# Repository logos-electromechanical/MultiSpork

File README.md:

MultiSpork
==========

A wireless analog/digital multitool &amp; data recorder.

When I'm working on a mobile robotics projects, I often wish I could attach my scope, logic analyzer, or signal generator to some aspect of the 'bot without tethering it to the bench. IOW, what I need is some kind of widget that does the data acquisition on the 'bot and sends it back to a screen. Ideally, it would also have plenty of range, easy configuration, a nice interface (Saleae is my model for how this should be). 

Maxim just released a chip, the MAX 11300, that incorporates a good chunk of what's required for this. It gives you twenty channels, each of which can by ADC, DAC, or GPIO, and communicates over a fast SPI bus. Add an Atmel SAM processor (I already have the dev tools, so this is an easy decision) and a wifi module, and we're in business. Cheap wifi-only Android tablets can be had for as little as $50, so Android is the obvious choice for a host OS. 

See the MultiSpork/documentation/MultiSporkSystemDescription.md for more info. This will go into the wiki when it's complete.

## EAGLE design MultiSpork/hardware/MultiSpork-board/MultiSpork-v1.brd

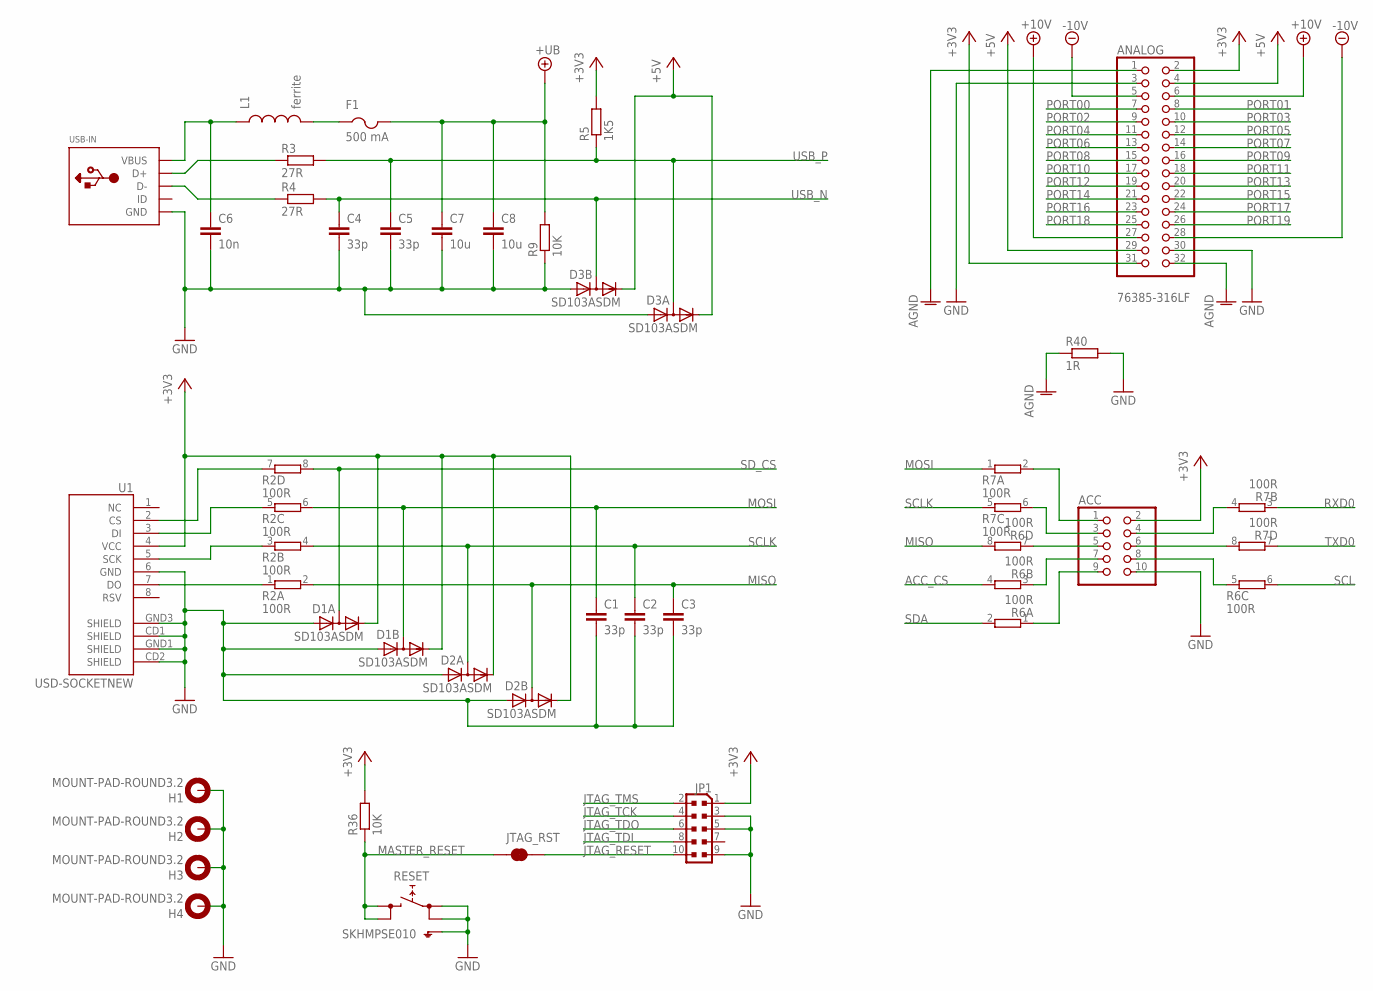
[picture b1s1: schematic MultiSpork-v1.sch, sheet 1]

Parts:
ACC: PINHD-2X5_2.54; 2X05; PARTNO *
ANALOG: 76385-316LF; 32P-SIDE-SMD; PARTNO 76385-316LF
C1, C2, C3, C4, C5: 33p; C0603; PARTNO VJ0603A330JXACW1BC
C6: 10n; C0603; PARTNO CL10B103KB8NCNC
C7, C8: 10u; C1206; PARTNO C3216X5R1E106M
D1, D2, D3: SD103ASDM; SOT26; PARTNO SD103ASDM-7
F1: 500 mA; R1206; PARTNO 1206L050/15YR
H1, H2, H3, H4: MOUNT-PAD-ROUND3.2; 3,2-PAD; PARTNO *
JP1: PINHEAD_PINHD-2X5PASSO127; PINHEAD_2X05_127; PARTNO M50-3500542
JTAG_RST: JUMPER-PAD-2-NC_BY_TRACE; PAD-JUMPER-2-NC_BY_TRACE_YES_SILK
L1: ferrite; 0805; PARTNO MI0805K400R-10
R2, R6, R7: 100R; CTS742C083-RES; PARTNO 742C083101JPTR
R3, R4: 27R; R0603; PARTNO CRCW060327R0FKEA
R5: 1K5; R0603; PARTNO ERJ-3GEYJ152V
R9, R36: 10K; R0603; PARTNO RNCP0603FTD10K0
R40: 1R; R1206; PARTNO CRCW12061R00FKEA
RESET: SKHMPSE010; SKHMPXE010; PARTNO SKHMQKE010
U1: USD-SOCKETNEW; MICRO-SD-SOCKET-PP; PARTNO 502570-0893
USB-IN: USBMINIB; USB-MINIB; PARTNO 20236

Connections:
+3V3: ACC.2, ANALOG.2, ANALOG.31, D1.2 (C), D1.5 (C), D2.2 (C), D2.5 (C), JP1.1, R5.2, R36.2, U1.4 (VCC); also elsewhere on the board
+5V: ANALOG.4, ANALOG.29, D3.2 (C), D3.5 (C); also elsewhere on the board
+10V: ANALOG.6, ANALOG.27; also elsewhere on the board
+UB: C7.1, C8.1, F1.2, R9.2; also elsewhere on the board
-10V: ANALOG.5, ANALOG.28; also elsewhere on the board
ACC_CS: R6.4 (2); also elsewhere on the board
AGND: ANALOG.1, ANALOG.32, R40.1; also elsewhere on the board
GND: ACC.10, ANALOG.3, ANALOG.30, C1.2, C2.2, C3.2, C4.2, C5.2, C6.2, C7.2, C8.2, D1.3 (A), D1.6 (A), D2.3 (A), D2.6 (A), D3.3 (A), D3.6 (A), H1.B3,2, H2.B3,2, H3.B3,2, H4.B3,2, JP1.3, JP1.5, JP1.9, R9.1, R40.2, RESET.1 (1.1), RESET.2 (1.2), RESET.5 (SH), U1.6 (GND), U1.CD1 (SHIELD), U1.CD2 (SHIELD), U1.GND1 (SHIELD), U1.GND3 (SHIELD), USB-IN.GND; also elsewhere on the board
JTAG_RESET: JP1.10, JTAG_RST.2
JTAG_TCK: JP1.4; also elsewhere on the board
JTAG_TDI: JP1.8; also elsewhere on the board
JTAG_TDO: JP1.6; also elsewhere on the board
JTAG_TMS: JP1.2; also elsewhere on the board
MASTER_RESET: JTAG_RST.1, R36.1, RESET.3 (2.1), RESET.4 (2.2); also elsewhere on the board
MISO: C3.1, D2.1 (AC), R2.2, R6.8 (2); also elsewhere on the board
MOSI: C1.1, D1.1 (AC), R2.6 (2), R7.1; also elsewhere on the board
unnamed: C6.1, L1.1, USB-IN.VBUS
unnamed: R2.7 (1), U1.2 (CS)
unnamed: R2.5 (1), U1.3 (DI)
unnamed: R2.3 (1), U1.5 (SCK)
unnamed: R2.1, U1.7 (DO)
unnamed: R3.1, USB-IN.D+
unnamed: R4.1, USB-IN.D-
unnamed: ACC.1, R7.2
unnamed: ACC.3, R7.6 (2)
unnamed: ACC.5, R6.7 (1)
unnamed: ACC.7, R6.3 (1)
unnamed: ACC.9, R6.1
unnamed: ACC.6, R7.8 (2)
unnamed: ACC.4, R7.4 (2)
unnamed: ACC.8, R6.5 (1)
unnamed: F1.1, L1.2
PORT00: ANALOG.7; also elsewhere on the board
PORT01: ANALOG.8; also elsewhere on the board
PORT02: ANALOG.9; also elsewhere on the board
PORT03: ANALOG.10; also elsewhere on the board
PORT04: ANALOG.11; also elsewhere on the board
PORT05: ANALOG.12; also elsewhere on the board
PORT06: ANALOG.13; also elsewhere on the board
PORT07: ANALOG.14; also elsewhere on the board
PORT08: ANALOG.15; also elsewhere on the board
PORT09: ANALOG.16; also elsewhere on the board
PORT10: ANALOG.17; also elsewhere on the board
PORT11: ANALOG.18; also elsewhere on the board
PORT12: ANALOG.19; also elsewhere on the board
PORT13: ANALOG.20; also elsewhere on the board
PORT14: ANALOG.21; also elsewhere on the board
PORT15: ANALOG.22; also elsewhere on the board
PORT16: ANALOG.23; also elsewhere on the board
PORT17: ANALOG.24; also elsewhere on the board
PORT18: ANALOG.25; also elsewhere on the board
PORT19: ANALOG.26; also elsewhere on the board
RXD0: R7.3 (1); also elsewhere on the board
SCL: R6.6 (2); also elsewhere on the board
SCLK: C2.1, D2.4 (AC), R2.4 (2), R7.5 (1); also elsewhere on the board
SDA: R6.2; also elsewhere on the board
SD_CS: D1.4 (AC), R2.8 (2); also elsewhere on the board
TXD0: R7.7 (1); also elsewhere on the board
USB_N: C4.1, D3.1 (AC), R4.2; also elsewhere on the board
USB_P: C5.1, D3.4 (AC), R3.2, R5.1; also elsewhere on the board

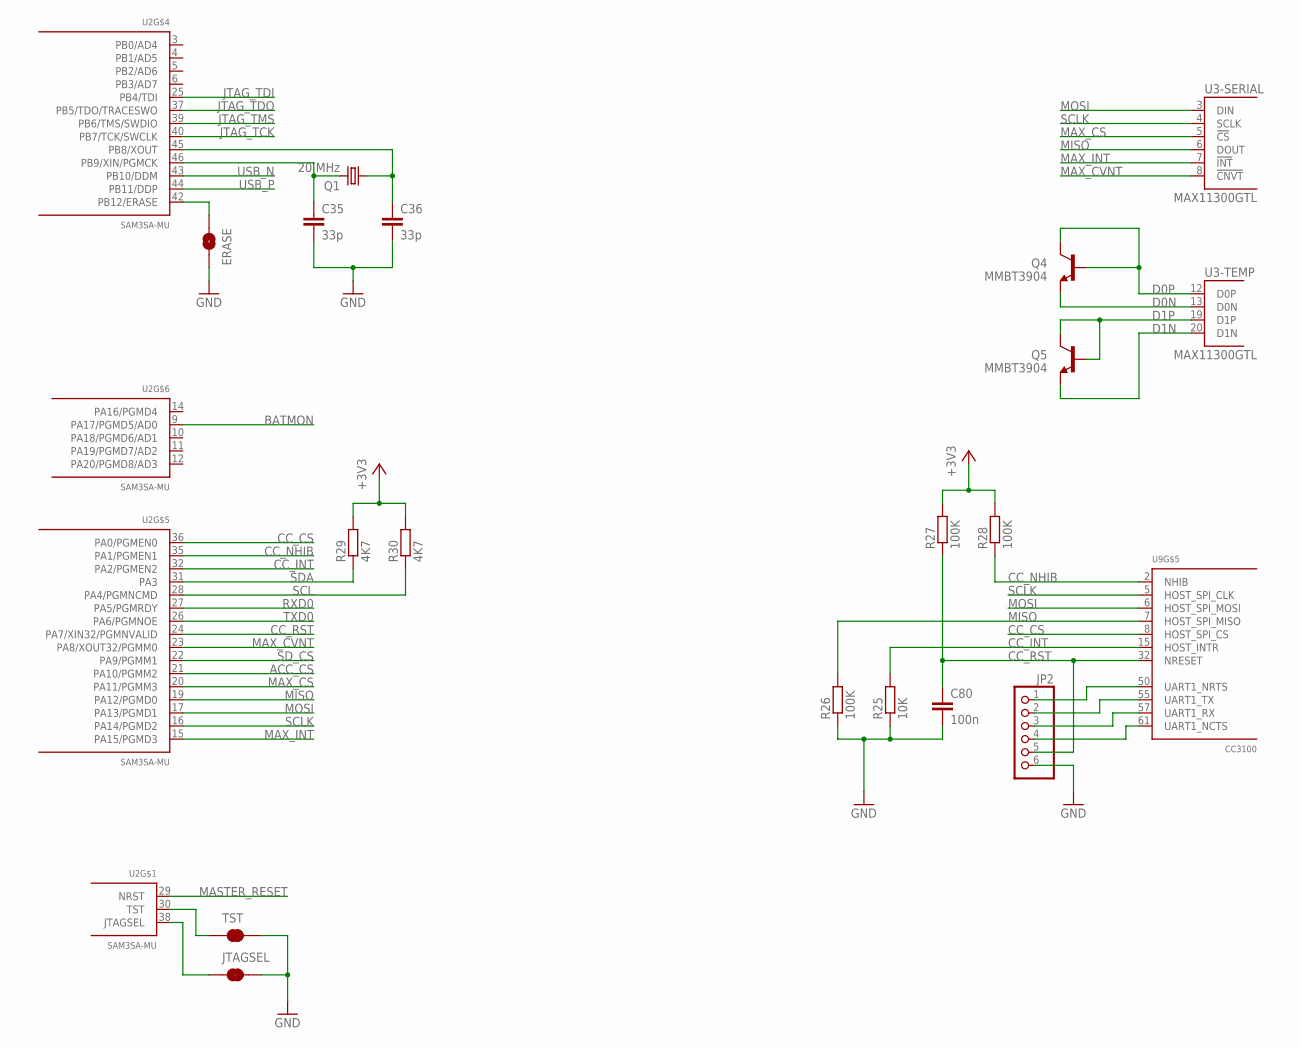
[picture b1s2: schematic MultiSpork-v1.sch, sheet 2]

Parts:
C35, C36: 33p; C0603; PARTNO VJ0603A330JXACW1BC
C80: 100n; C0603; PARTNO CC0603KRX7R9BB104
ERASE: JUMPER-PAD-2-NOYES_SILK; PAD-JUMPER-2-NO_YES_SILK
JP2: PINHD-1X6; 1X06; PARTNO *
JTAGSEL: JUMPER-PAD-2-NC_BY_TRACE; PAD-JUMPER-2-NC_BY_TRACE_YES_SILK
Q1: 20 MHz; CSM-3X; PARTNO ECS-200-20-3X-TR
Q4, Q5: MMBT3904; SOT23; PARTNO MMBT3904
R25: 10K; R0603; PARTNO RNCP0603FTD10K0
R26, R27, R28: 100K; R0603; PARTNO CRCW0603100KFKEA
R29, R30: 4K7; R0603; PARTNO RC1608J472CS
TST: JUMPER-PAD-2-NC_BY_TRACE; PAD-JUMPER-2-NC_BY_TRACE_YES_SILK
U2: SAM3SA-MU; QFN48; PARTNO ATSAM3S4AA-MU
U3: MAX11300GTL; TQFN40; PARTNO MAX11300GTL+
U9: CC3100; QFN64; PARTNO CC3100

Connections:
+3V3: R27.2, R28.2, R29.2, R30.2; also elsewhere on the board
ACC_CS: U2.21 (PA10/PGMM2); also elsewhere on the board
BATMON: U2.9 (PA17/PGMD5/AD0); also elsewhere on the board
CC_CS: U2.36 (PA0/PGMEN0), U9.8 (HOST_SPI_CS)
CC_INT: R25.2, U2.32 (PA2/PGMEN2), U9.15 (HOST_INTR)
CC_NHIB: R28.1, U2.35 (PA1/PGMEN1), U9.2 (NHIB)
CC_RST: C80.1, JP2.5, R27.1, U2.24 (PA7/XIN32/PGMNVALID), U9.32 (NRESET)
D0N: Q4.2 (E), U3.13 (D0N)
D0P: Q4.1 (B), Q4.3 (C), U3.12 (D0P)
D1N: Q5.2 (E), U3.20 (D1N)
D1P: Q5.1 (B), Q5.3 (C), U3.19 (D1P)
DCDC_ANA2_SW_N: U9.46 (DCDC_ANA2_SW_N)
DCDC_ANA2_SW_P: U9.45 (DCDC_ANA2_SW_P)
GND: C35.2, C36.2, C80.2, ERASE.2, JP2.6, JTAGSEL.2, R25.1, R26.1, TST.2; also elsewhere on the board
JTAG_TCK: U2.40 (PB7/TCK/SWCLK); also elsewhere on the board
JTAG_TDI: U2.25 (PB4/TDI); also elsewhere on the board
JTAG_TDO: U2.37 (PB5/TDO/TRACESWO); also elsewhere on the board
JTAG_TMS: U2.39 (PB6/TMS/SWDIO); also elsewhere on the board
MASTER_RESET: U2.29 (NRST); also elsewhere on the board
MAX_CS: U2.20 (PA11/PGMM3), U3.5 (!CS!)
MAX_CVNT: U2.23 (PA8/XOUT32/PGMM0), U3.8 (!CNVT!)
MAX_INT: U2.15 (PA15/PGMD3), U3.7 (!INT!)
MISO: R26.2, U2.19 (PA12/PGMD0), U3.6 (DOUT), U9.7 (HOST_SPI_MISO); also elsewhere on the board
MOSI: U2.17 (PA13/PGMD1), U3.3 (DIN), U9.6 (HOST_SPI_MOSI); also elsewhere on the board
unnamed: C35.1, Q1.2, U2.46 (PB9/XIN/PGMCK)
unnamed: C36.1, Q1.1, U2.45 (PB8/XOUT)
unnamed: TST.1, U2.30 (TST)
unnamed: JTAGSEL.1, U2.38 (JTAGSEL)
unnamed: ERASE.1, U2.42 (PB12/ERASE)
unnamed: JP2.1, U9.50 (UART1_NRTS)
unnamed: JP2.2, U9.55 (UART1_TX)
unnamed: JP2.3, U9.57 (UART1_RX)
unnamed: JP2.4, U9.61 (UART1_NCTS)
RXD0: U2.27 (PA5/PGMRDY); also elsewhere on the board
SCL: R30.1, U2.28 (PA4/PGMNCMD); also elsewhere on the board
SCLK: U2.16 (PA14/PGMD2), U3.4 (SCLK), U9.5 (HOST_SPI_CLK); also elsewhere on the board
SDA: R29.1, U2.31 (PA3); also elsewhere on the board
SD_CS: U2.22 (PA9/PGMM1); also elsewhere on the board
TXD0: U2.26 (PA6/PGMNOE); also elsewhere on the board
USB_N: U2.43 (PB10/DDM); also elsewhere on the board
USB_P: U2.44 (PB11/DDP); also elsewhere on the board

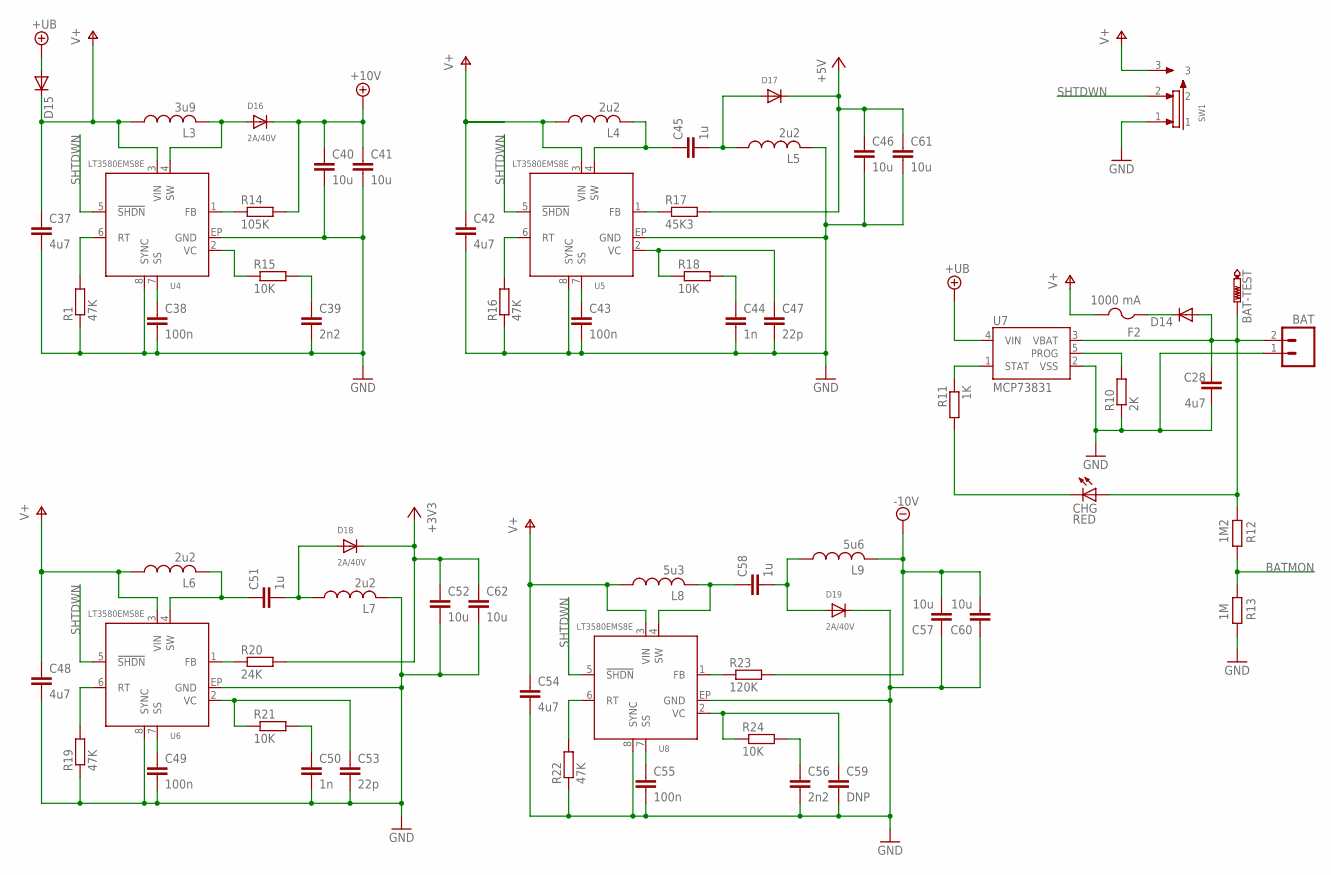
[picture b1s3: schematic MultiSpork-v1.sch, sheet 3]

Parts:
BAT: M02-JST-2MM-SMT; S2B-PH; PARTNO S2B-PH-SM4-TB(LF)(SN)
BAT-TEST: PTR1TP13SQ; TP13SQ; PARTNO TP13
C28: 4u7; C1206; PARTNO C3216Y5V1H475Z
C37, C42, C48, C54: 4u7; C1210; PARTNO TMK325B7475KN-T
C38, C43, C49, C55: 100n; C0603; PARTNO CC0603KRX7R9BB104
C39, C56: 2n2; C0603; PARTNO VJ0603Y222KXACW1BC
C40, C41, C46, C52, C57, C60, C61, C62: 10u; C1210; PARTNO UMK325BJ106MM
C44, C50: 1n; C0603; PARTNO UMK107SD102KA-T
C45, C51, C58: 1u; C1210; PARTNO TMK325B7105KD-T
C47, C53: 22p; C0603; PARTNO GQM1885C1H220JB01D
C59: DNP; C0603; PARTNO DNP
CHG: RED; CHIP-LED0603; PARTNO LTST-C193KRKT-5A
D14, D15: DIODE-SMB; SMB; PARTNO LSM115JE3
D16, D18, D19: 2A/40V; SMADIODE; PARTNO CD214A-B240LLF
D17: DIODESOD-123; SOD-123; PARTNO PMEG3020ER,115
F2: 1000 mA; R1206; PARTNO 0ZCJ0100FF2E
L3: 3u9; L2323; PARTNO SRR5018-3R9Y
L4, L5, L6, L7: 2u2; L1008; PARTNO 252012CDMCDS-2R2MC
L8: 5u3; L2323; PARTNO SRR5028-5R3Y
L9: 5u6; L1008; PARTNO 1008 (2520 metric)
R1, R16, R19, R22: 47K; R0603; PARTNO MCT06030C4702FP500
R10: 2K; R0603; PARTNO RC0603FR-072KL
R11: 1K; R0603; PARTNO RMCF0603FT1K00
R12: 1M2; R0603; PARTNO ERJ-3EKF1204V
R13: 1M; R0603; PARTNO ERJ-3EKF1004V
R14: 105K; R0603; PARTNO CRCW0603105KFKEA
R15, R18, R21, R24: 10K; R0603; PARTNO RNCP0603FTD10K0
R17: 45K3; R0603; PARTNO CRCW060345K3FKEA
R20: 24K; R0603; PARTNO CRCW060324K0FKEA
R23: 120K; R0603; PARTNO AF0603FR-07120KL
SW1: JS102011SAQN; PARTNO JS102011SAQN
U4, U5, U6, U8: LT3580EMS8E; MSOP8; PARTNO LT3580EMS8E#PBF
U7: MCP73831; SOT23-5; PARTNO MCP73831T-2ACI/OT

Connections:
+3V3: C52.1, C62.1, D18.C, R20.2; also elsewhere on the board
+5V: C46.1, C61.1, D17.C, R17.2; also elsewhere on the board
+10V: C40.1, C41.1, D16.C, R14.2; also elsewhere on the board
+UB: D15.A, U7.4 (VIN); also elsewhere on the board
-10V: C57.2, C60.2, L9.2, R23.2; also elsewhere on the board
BATMON: R12.2, R13.1; also elsewhere on the board
GND: BAT.1, C28.2, C37.2, C38.2, C39.2, C40.2, C41.2, C42.2, C43.2, C44.2, C46.2, C47.2, C48.2, C49.2, C50.2, C52.2, C53.2, C54.2, C55.2, C56.2, C57.1, C59.2, C60.1, C61.2, C62.2, D19.C, L5.2, L7.2, R1.1, R10.1, R13.2, R16.1, R19.1, R22.1, SW1.1, U4.8 (SYNC), U4.EP (GND), U5.8 (SYNC), U5.EP (GND), U6.8 (SYNC), U6.EP (GND), U7.2 (VSS), U8.8 (SYNC), U8.EP (GND); also elsewhere on the board
unnamed: C38.1, U4.7 (SS)
unnamed: R1.2, U4.6 (RT)
unnamed: R14.1, U4.1 (FB)
unnamed: R15.1, U4.2 (VC)
unnamed: C39.1, R15.2
unnamed: C43.1, U5.7 (SS)
unnamed: D16.A, L3.4 (2), U4.4 (SW)
unnamed: R16.2, U5.6 (RT)
unnamed: R17.1, U5.1 (FB)
unnamed: R10.2, U7.5 (PROG)
unnamed: R11.1, U7.1 (STAT)
unnamed: CHG.C, R11.2
unnamed: D14.C, F2.1
unnamed: C47.1, R18.1, U5.2 (VC)
unnamed: C44.1, R18.2
unnamed: C45.1, L4.2, U5.4 (SW)
unnamed: C45.2, D17.A, L5.1
unnamed: C55.1, U8.7 (SS)
unnamed: R22.2, U8.6 (RT)
unnamed: R23.1, U8.1 (FB)
unnamed: C49.1, U6.7 (SS)
unnamed: R19.2, U6.6 (RT)
unnamed: R20.1, U6.1 (FB)
unnamed: C53.1, R21.1, U6.2 (VC)
unnamed: C50.1, R21.2
unnamed: C51.1, L6.2, U6.4 (SW)
unnamed: C51.2, D18.A, L7.1
unnamed: C59.1, R24.1, U8.2 (VC)
unnamed: C56.1, R24.2
unnamed: C58.1, L8.4 (2), U8.4 (SW)
unnamed: C58.2, D19.A, L9.1
SHTDWN: SW1.2, U4.5 (!SHDN!), U5.5 (!SHDN!), U6.5 (!SHDN!), U8.5 (!SHDN!)
V+: C37.1, C42.1, C48.1, C54.1, D15.C, F2.2, L3.3 (1), L4.1, L6.1, L8.3 (1), SW1.3, U4.3 (VIN), U5.3 (VIN), U6.3 (VIN), U8.3 (VIN)
VBAT1: BAT.2, BAT-TEST.TP, C28.1, CHG.A, D14.A, R12.1, U7.3 (VBAT)

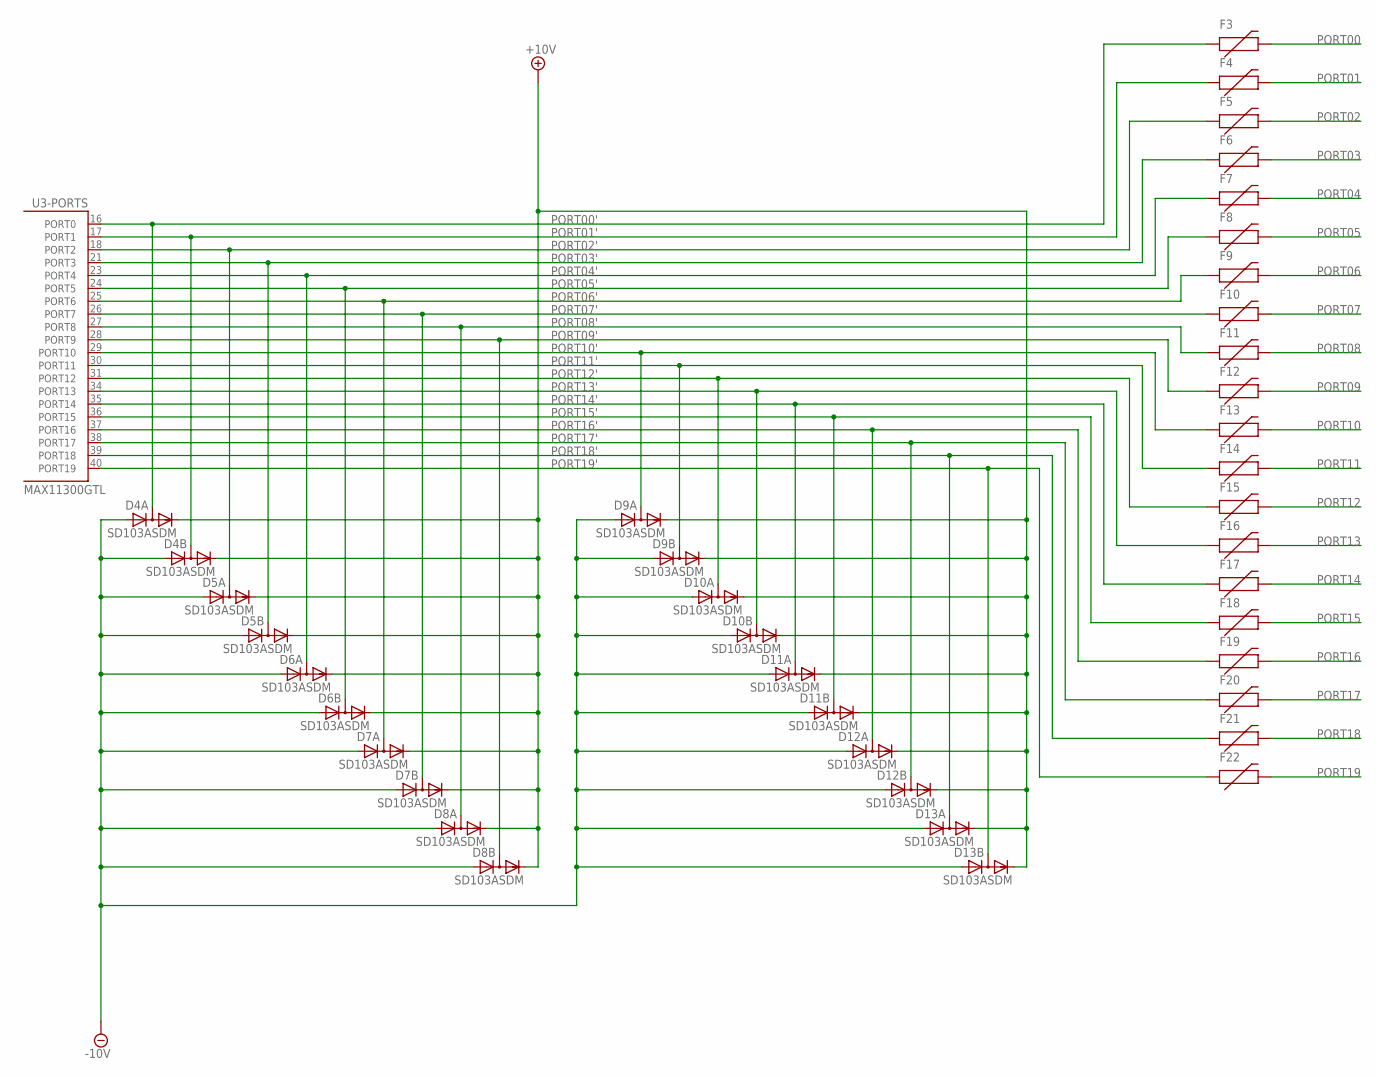
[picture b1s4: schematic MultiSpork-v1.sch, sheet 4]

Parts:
D4, D5, D6, D7, D8, D9, D10, D11, D12, D13: SD103ASDM; SOT26; PARTNO SD103ASDM-7
F3, F4, F5, F6, F7, F8, F9, F10, F11, F12, F13, F14, F15, F16, F17, F18, F19, F20, F21, F22: PTC0603; 0603; PARTNO femtoSMDC008F-02
U3: MAX11300GTL; TQFN40; PARTNO MAX11300GTL+

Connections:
+10V: D4.2 (C), D4.5 (C), D5.2 (C), D5.5 (C), D6.2 (C), D6.5 (C), D7.2 (C), D7.5 (C), D8.2 (C), D8.5 (C), D9.2 (C), D9.5 (C), D10.2 (C), D10.5 (C), D11.2 (C), D11.5 (C), D12.2 (C), D12.5 (C), D13.2 (C), D13.5 (C); also elsewhere on the board
-10V: D4.3 (A), D4.6 (A), D5.3 (A), D5.6 (A), D6.3 (A), D6.6 (A), D7.3 (A), D7.6 (A), D8.3 (A), D8.6 (A), D9.3 (A), D9.6 (A), D10.3 (A), D10.6 (A), D11.3 (A), D11.6 (A), D12.3 (A), D12.6 (A), D13.3 (A), D13.6 (A); also elsewhere on the board
PORT00: F3.2; also elsewhere on the board
PORT00': D4.4 (AC), F3.1, U3.16 (PORT0)
PORT01: F4.2; also elsewhere on the board
PORT01': D4.1 (AC), F4.1, U3.17 (PORT1)
PORT02: F5.2; also elsewhere on the board
PORT02': D5.4 (AC), F5.1, U3.18 (PORT2)
PORT03: F6.2; also elsewhere on the board
PORT03': D5.1 (AC), F6.1, U3.21 (PORT3)
PORT04: F7.2; also elsewhere on the board
PORT04': D6.4 (AC), F7.1, U3.23 (PORT4)
PORT05: F8.2; also elsewhere on the board
PORT05': D6.1 (AC), F8.1, U3.24 (PORT5)
PORT06: F9.2; also elsewhere on the board
PORT06': D7.4 (AC), F9.1, U3.25 (PORT6)
PORT07: F10.2; also elsewhere on the board
PORT07': D7.1 (AC), F10.1, U3.26 (PORT7)
PORT08: F11.2; also elsewhere on the board
PORT08': D8.4 (AC), F11.1, U3.27 (PORT8)
PORT09: F12.2; also elsewhere on the board
PORT09': D8.1 (AC), F12.1, U3.28 (PORT9)
PORT10: F13.2; also elsewhere on the board
PORT10': D9.4 (AC), F13.1, U3.29 (PORT10)
PORT11: F14.2; also elsewhere on the board
PORT11': D9.1 (AC), F14.1, U3.30 (PORT11)
PORT12: F15.2; also elsewhere on the board
PORT12': D10.4 (AC), F15.1, U3.31 (PORT12)
PORT13: F16.2; also elsewhere on the board
PORT13': D10.1 (AC), F16.1, U3.34 (PORT13)
PORT14: F17.2; also elsewhere on the board
PORT14': D11.4 (AC), F17.1, U3.35 (PORT14)
PORT15: F18.2; also elsewhere on the board
PORT15': D11.1 (AC), F18.1, U3.36 (PORT15)
PORT16: F19.2; also elsewhere on the board
PORT16': D12.4 (AC), F19.1, U3.37 (PORT16)
PORT17: F20.2; also elsewhere on the board
PORT17': D12.1 (AC), F20.1, U3.38 (PORT17)
PORT18: F21.2; also elsewhere on the board
PORT18': D13.4 (AC), F21.1, U3.39 (PORT18)
PORT19: F22.2; also elsewhere on the board
PORT19': D13.1 (AC), F22.1, U3.40 (PORT19)

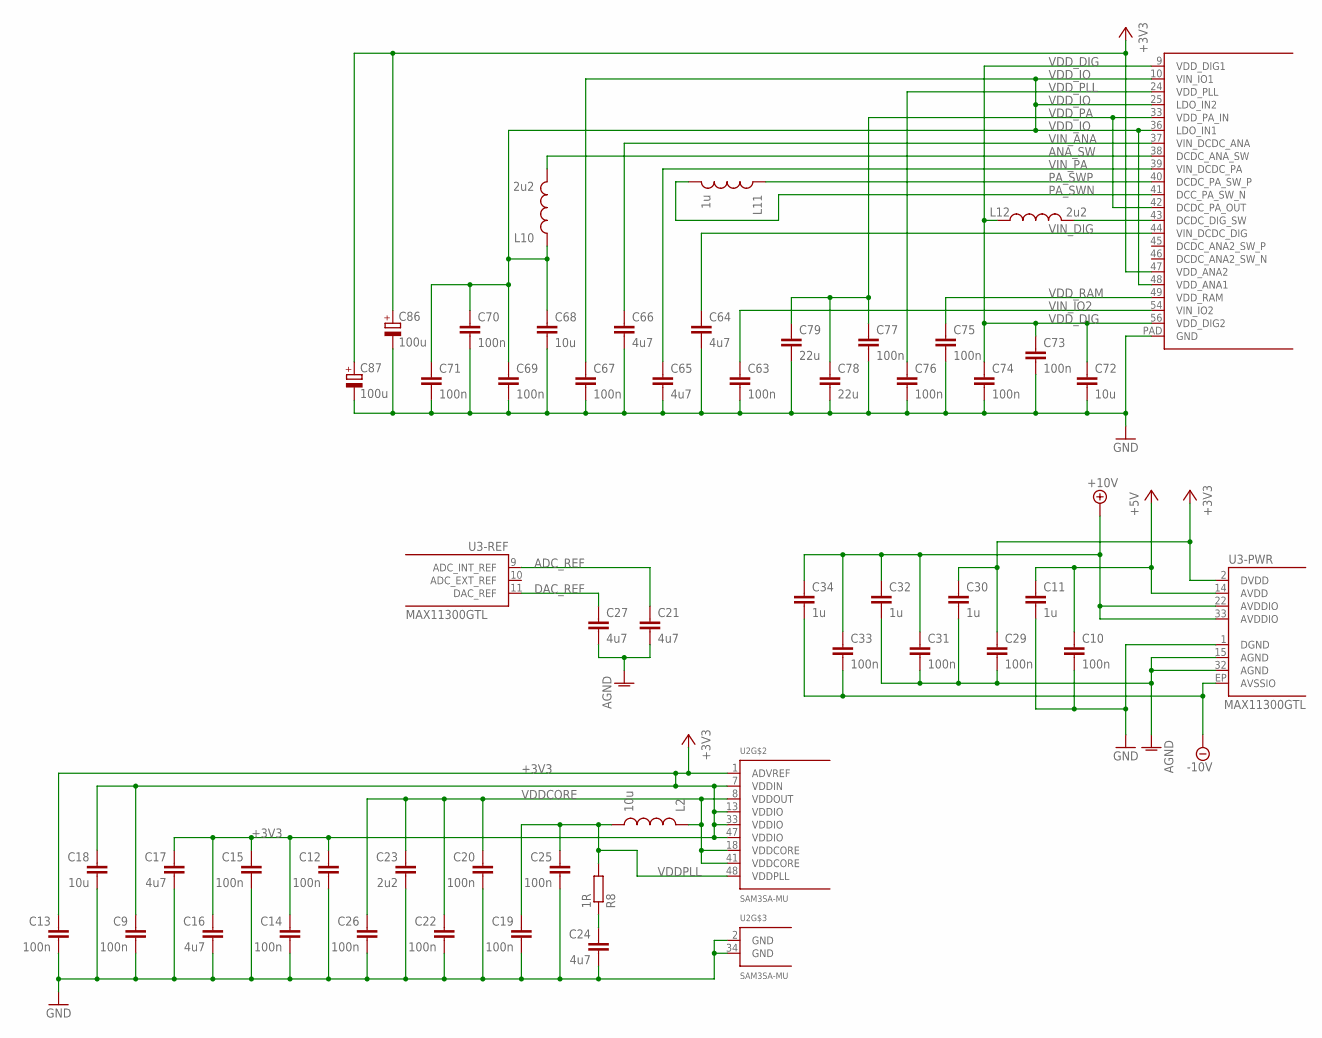
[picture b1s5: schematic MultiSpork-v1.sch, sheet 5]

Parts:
C9, C10, C12, C13, C14, C15, C19, C20, C22, C25, C26, C29, C31, C33, C63, C67, C69, C70, C71, C73, C74, C75, C76, C77: 100n; C0603; PARTNO CC0603KRX7R9BB104
C11, C30, C32, C34: 1u; C0603; PARTNO UMK107BJ105KA-T
C16, C17, C21, C24, C27, C64, C65, C66: 4u7; C0603; PARTNO GRM188F51A475ZE20D
C18, C68, C72: 10u; C0603; PARTNO EMK107BBJ106MA-T
C23: 2u2; C0603; PARTNO C1608X7R1A225K
C78, C79: 22u; C1206; PARTNO GRM31CR61C226ME15L
C86, C87: 100u; CT6032; PARTNO TAJC107K016RNJ
L2: 10u; INDUCTOR-1206; PARTNO LQH31CN100K03L
L10, L12: 2u2; INDUCTOR-1206; PARTNO LQM31PN2R2M00L
L11: 1u; INDUCTOR-1206; PARTNO LQM31PN1R0MC0L
R8: 1R; R0603; PARTNO ERJ-3GEYJ1R0V
U2: SAM3SA-MU; QFN48; PARTNO ATSAM3S4AA-MU
U3: MAX11300GTL; TQFN40; PARTNO MAX11300GTL+
U9: CC3100; QFN64; PARTNO CC3100

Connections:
+3V3: C9.1, C12.1, C13.1, C14.1, C15.1, C16.1, C17.1, C18.1, C29.1, C30.1, C86.+, C87.+, U2.1 (ADVREF), U2.7 (VDDIN), U2.13 (VDDIO), U2.33 (VDDIO), U2.47 (VDDIO), U3.2 (DVDD), U9.47 (VDD_ANA2); also elsewhere on the board
+5V: C10.1, C11.1, U3.14 (AVDD); also elsewhere on the board
+10V: C31.1, C32.1, C33.1, C34.1, U3.22 (AVDDIO), U3.33 (AVDDIO); also elsewhere on the board
-10V: C33.2, C34.2, U3.EP (AVSSIO); also elsewhere on the board
ADC_REF: C21.1, U3.9 (ADC_INT_REF)
AGND: C21.2, C27.2, C29.2, C30.2, C31.2, C32.2, U3.15 (AGND), U3.32 (AGND); also elsewhere on the board
ANA_SW: L10.P$2 (2), U9.38 (DCDC_ANA_SW)
DAC_REF: C27.1, U3.11 (DAC_REF)
DCDC_ANA2_SW_N: U9.46 (DCDC_ANA2_SW_N)
DCDC_ANA2_SW_P: U9.45 (DCDC_ANA2_SW_P)
GND: C9.2, C10.2, C11.2, C12.2, C13.2, C14.2, C15.2, C16.2, C17.2, C18.2, C19.2, C20.2, C22.2, C23.2, C24.2, C25.2, C26.2, C63.2, C64.2, C65.2, C66.2, C67.2, C68.2, C69.2, C70.2, C71.2, C72.2, C73.2, C74.2, C75.2, C76.2, C77.2, C78.2, C79.2, C86.-, C87.-, U2.2 (GND), U2.34 (GND), U3.1 (DGND), U9.PAD (GND); also elsewhere on the board
unnamed: L12.P$2 (2), U9.43 (DCDC_DIG_SW)
PA_SWN: L11.P$2 (2), U9.41 (DCC_PA_SW_N)
PA_SWP: L11.P$1 (1), U9.40 (DCDC_PA_SW_P)
PLL-GND: C24.1, R8.1
VDDCORE: C20.1, C22.1, C23.1, C26.1, L2.P$1 (1), U2.8 (VDDOUT), U2.18 (VDDCORE), U2.41 (VDDCORE)
VDDPLL: C19.1, C25.1, L2.P$2 (2), R8.2, U2.48 (VDDPLL)
VDD_DIG: C72.1, C73.1, C74.1, L12.P$1 (1), U9.9 (VDD_DIG1), U9.56 (VDD_DIG2)
VDD_IO: C67.1, C68.1, C69.1, C70.1, C71.1, L10.P$1 (1), U9.10 (VIN_IO1), U9.25 (LDO_IN2), U9.36 (LDO_IN1), U9.48 (VDD_ANA1)
VDD_PA: C77.1, C78.1, C79.1, U9.33 (VDD_PA_IN), U9.42 (DCDC_PA_OUT)
VDD_PLL: C76.1, U9.24 (VDD_PLL)
VDD_RAM: C75.1, U9.49 (VDD_RAM)
VIN_ANA: C66.1, U9.37 (VIN_DCDC_ANA)
VIN_DIG: C64.1, U9.44 (VIN_DCDC_DIG)
VIN_IO2: C63.1, U9.54 (VIN_IO2)
VIN_PA: C65.1, U9.39 (VIN_DCDC_PA)

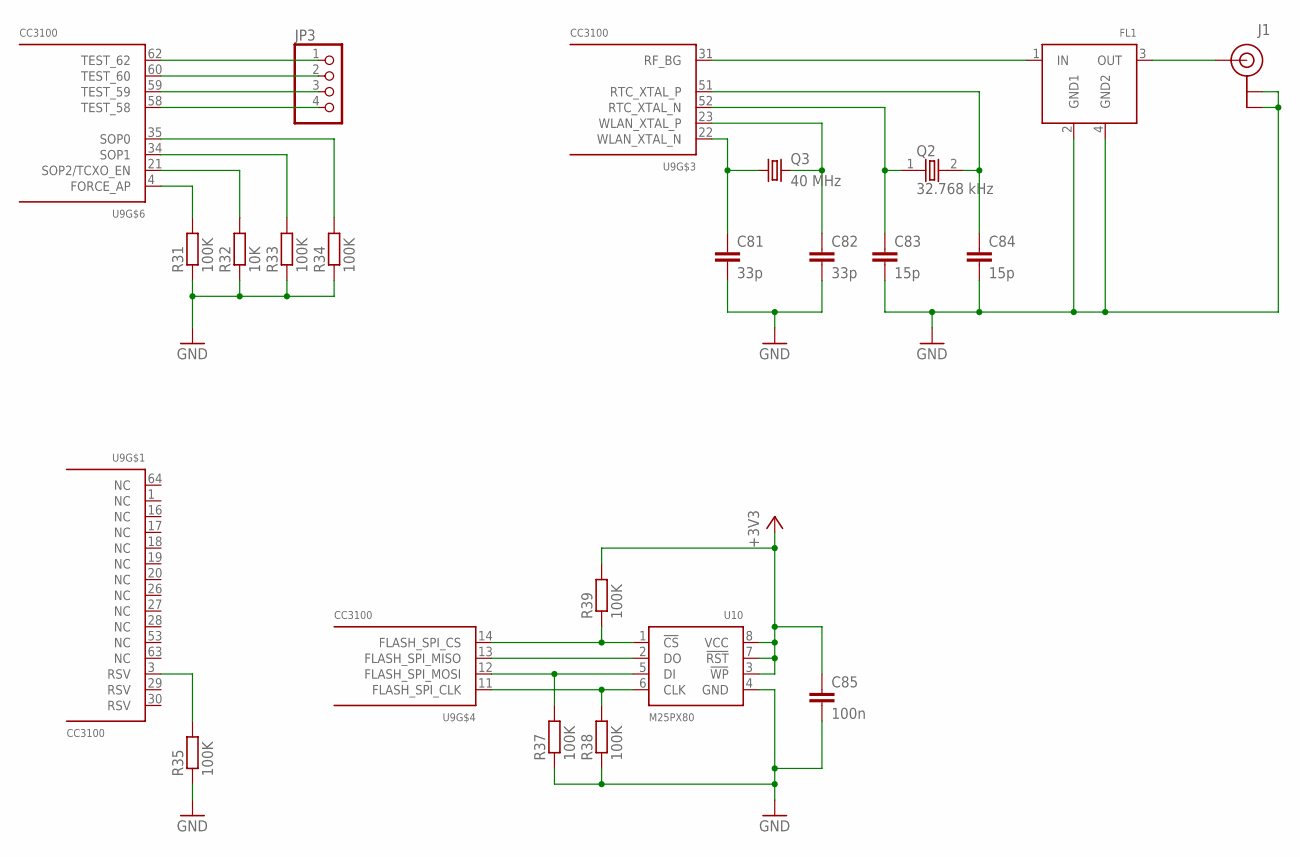
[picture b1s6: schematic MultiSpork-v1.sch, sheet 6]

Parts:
C81, C82: 33p; C0603; PARTNO VJ0603A330JXACW1BC
C83, C84: 15p; C0603; PARTNO VJ0603A150JXACW1BC
C85: 100n; C0603; PARTNO CC0603KRX7R9BB104
FL1: DEA202450BT; PARTNO DEA202450BT-7210A1
J1: U.FL; PARTNO U.FL-R-SMT(10)
JP3: PINHD-1X4; 1X04; PARTNO *
Q2: 32.768 kHz; ECX-31B; PARTNO ECS-.327-7-34B-TR
Q3: 40 MHz; CSM-3X; PARTNO ECS-400-20-3X-EN-TR
R31, R33, R34, R35, R37, R38, R39: 100K; R0603; PARTNO CRCW0603100KFKEA
R32: 10K; R0603; PARTNO RNCP0603FTD10K0
U9: CC3100; QFN64; PARTNO CC3100
U10: M25PX80; SOIC8; PARTNO M25PX80-VMN6TP

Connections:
+3V3: C85.1, R39.2, U10.3 (!WP!), U10.7 (!RST!), U10.8 (VCC); also elsewhere on the board
DCDC_ANA2_SW_N: U9.46 (DCDC_ANA2_SW_N)
DCDC_ANA2_SW_P: U9.45 (DCDC_ANA2_SW_P)
GND: C81.2, C82.2, C83.2, C84.2, C85.2, FL1.2 (GND1), FL1.4 (GND2), J1.P$1 (GND), J1.P$2 (GND), R31.1, R32.1, R33.1, R34.1, R35.1, R37.1, R38.1, U10.4 (GND); also elsewhere on the board
unnamed: R38.2, U9.11 (FLASH_SPI_CLK), U10.6 (CLK)
unnamed: R31.2, U9.4 (FORCE_AP)
unnamed: R32.2, U9.21 (SOP2/TCXO_EN)
unnamed: R33.2, U9.34 (SOP1)
unnamed: R34.2, U9.35 (SOP0)
unnamed: R37.2, U9.12 (FLASH_SPI_MOSI), U10.5 (DI)
unnamed: JP3.1, U9.62 (TEST_62)
unnamed: JP3.2, U9.60 (TEST_60)
unnamed: JP3.3, U9.59 (TEST_59)
unnamed: JP3.4, U9.58 (TEST_58)
unnamed: R35.2, U9.3 (RSV)
unnamed: C81.1, Q3.1, U9.22 (WLAN_XTAL_N)
unnamed: C82.1, Q3.2, U9.23 (WLAN_XTAL_P)
unnamed: C83.1, Q2.1, U9.52 (RTC_XTAL_N)
unnamed: C84.1, Q2.2, U9.51 (RTC_XTAL_P)
unnamed: U9.13 (FLASH_SPI_MISO), U10.2 (DO)
unnamed: R39.1, U9.14 (FLASH_SPI_CS), U10.1 (!CS!)
unnamed: FL1.1 (IN), U9.31 (RF_BG)
unnamed: FL1.3 (OUT), J1.P$3 (SIGNAL)

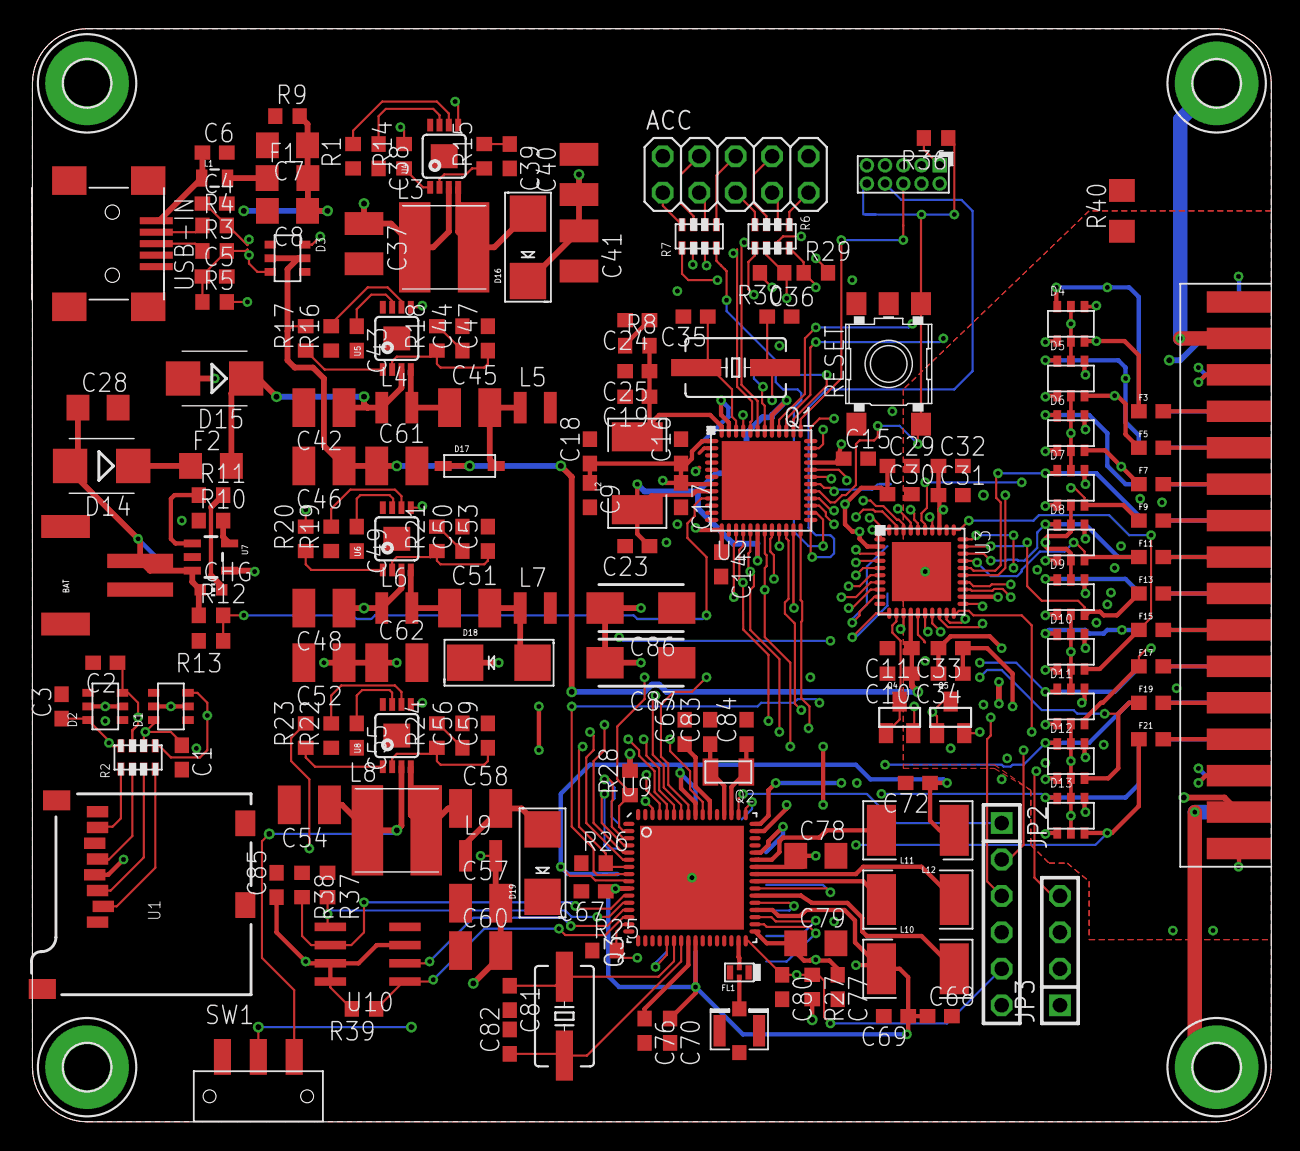
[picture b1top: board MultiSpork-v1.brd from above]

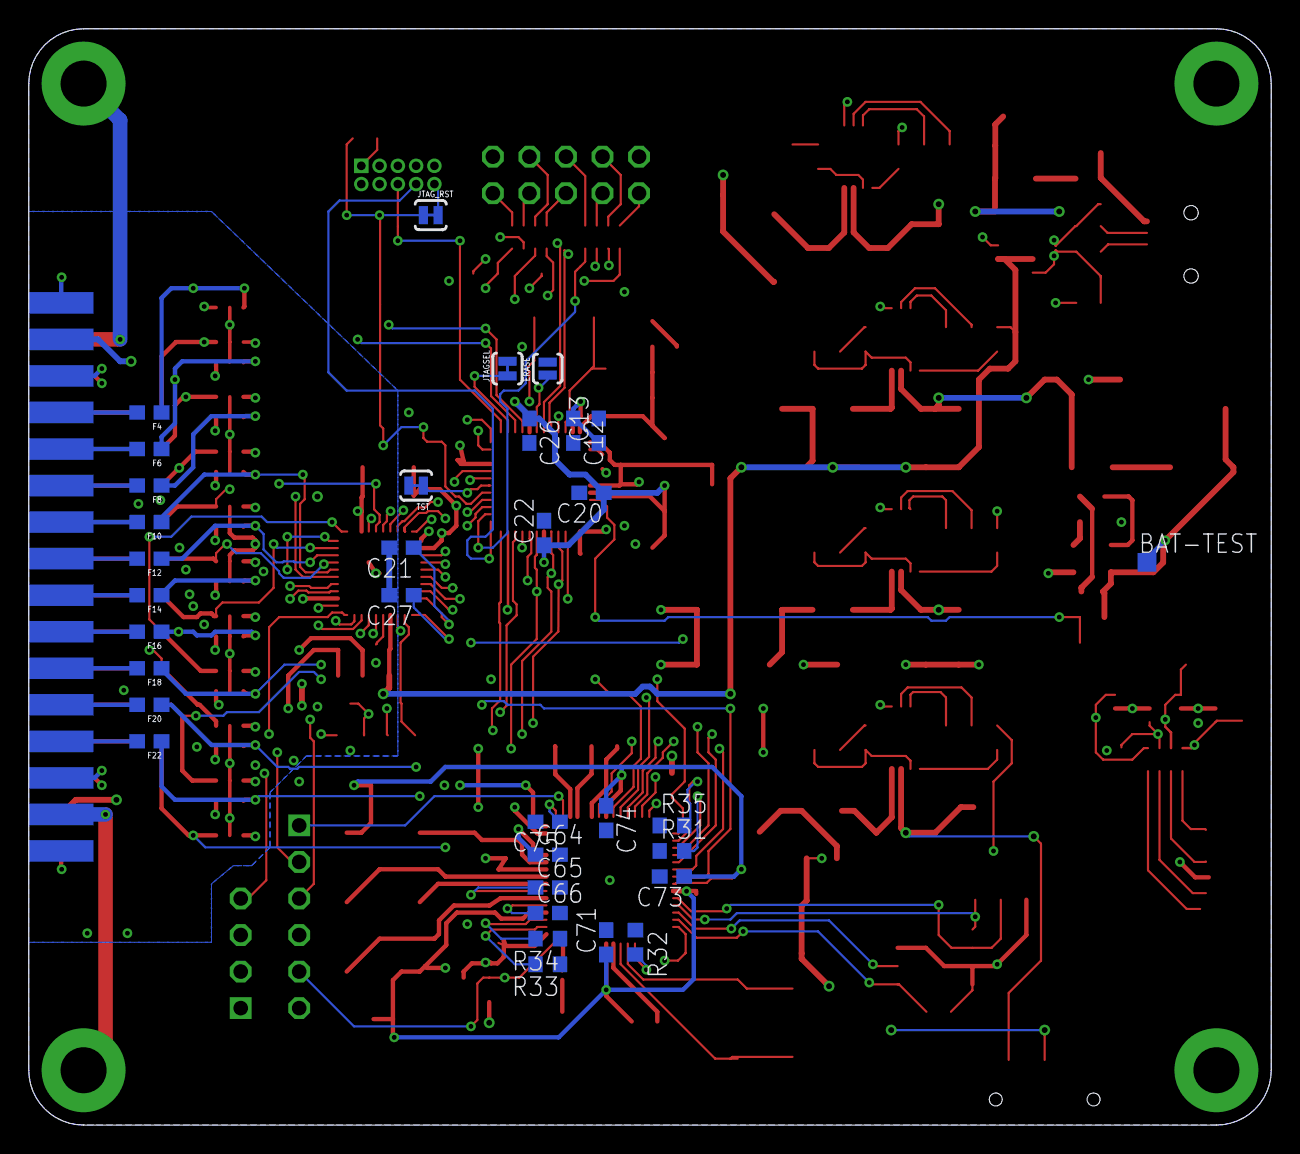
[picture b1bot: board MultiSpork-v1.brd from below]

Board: 4 copper layers, 86.4 x 76.2 mm, 216 parts (34 on the bottom side), 172 nets.

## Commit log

2014-07-19 Update README.md
    Copied in the thumbnail description from the Hackaday project entry.
2014-07-19 Update README.md
    Added wiki link
2014-07-19 Adding datasheets
2014-07-19 Added a hardware block diagram
2014-07-26 First check-in of schematic, board, and special libraries
2014-07-26 Adding a few more datasheets...
2014-07-26 First check-in of switching regulator design sheet for the LT3580
2014-07-26 Updated hardware block diagram such that: -- External power is through USB or battery -- Adding a battery charger block
2014-07-28 Finished design sheet to use a common design for all four regulators
2014-07-28 Added library for CC3100 and related parts
2014-07-28 Updated board with: -- Voltage regulators -- CC3100 WiFi
2014-07-28 -- Added flash chip to CC3100.lbr -- Added 2.4 GHz filter to CC3100.lbr -- Added RF components on schematic -- Added CC3100 crystals on schematic -- Added MAX11300 external temperature sensors -- Fix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
2014-07-31 Updated regulator design sheet to use smaller inductors
2014-07-31 Added datasheet for the serial flash required by the CC3100
2014-07-31 Finished schematic & placement for the prototype
2014-07-31 Shrank the board from 3x4 to 3x3.4
2014-08-02 -- Updated MAX11300 footprint with rounded pads to account for minimum clearances at the corners -- Added a switch to turn the regulators on and off -- Routed USB -- Routed SPI busses -- Routed analo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
2014-08-03 Finished routing
2014-08-13 Added a system description document
2014-08-13 Update README.md
    Updating link to more information
2014-08-16 Adding firmware descriptions (still in work)
2014-08-17 Further progress on firmware and host app definitions
2014-08-20 Create LICENSE.md
    Added the Apache License because we need something.
2014-08-20 -- Updated system description -- Added case mockup files -- Current routed picture
2014-08-24 More work on the system description
2015-01-21 .\s5uqt2as.xa0.txt
2015-01-21 .\rw4oldqi.irh.txt
2015-01-21 Added some more buffer data...
2015-01-31 .\zeyqqiop.s5q.txt
2015-01-31 Update MultiSporkComms.md
    Added network parameters
2015-01-31 Update MultiSporkComms.md
    -- Added buffer descriptions
    -- Added channel range descriptions
2015-06-30 Fixed multispork.capnp so it compiles Committing capnp compile -oc++ output
2015-06-30 updating MAX11300 datasheet

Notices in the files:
parts and their libraries:
SparkFun-Passives: Licensing: CC v3.0 Share-Alike You are welcome to use this library for commercial purposes.
SparkFun-PowerIC: Licensing: Creative Commons ShareAlike 4.0 International - https://creativecommons.org/licenses/by-sa/4.0
